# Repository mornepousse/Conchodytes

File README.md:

<h1 align="center">Conchodytes</h1>

<p align="center">
  <em>The shrimp that lives inside another's shell.</em><br>
  <em>La crevette qui vit dans la coquille d'un autre.</em>
</p>

---

## Firmware

The mouse runs the [KeSp firmware](https://github.com/mornepousse/KeSp_firmware)
(role `MOUSE`: PMW3389, three clicks, wheel, HID relayed to the dongle's slot 2).
Since 2026-09-21 **its board lives here**, not in the firmware repository:

- `boards/conchodytes/` — `board.h` (pinout, netlist-checked), `sdkconfig.defaults`,
  `test_pins.c` (the pinout contract);
- `firmware/` — the KeSp firmware as a git submodule, pinned on a release
  (`git submodule update --init`);
- `.github/workflows/firmware.yml` — calls the firmware's reusable workflow:
  every push builds `conchodytes_<version>.bin` (+ `_full.bin`), a `v*` tag
  publishes a release here.

```bash
scripts/test-pins.sh                                    # pinout contract, host, no toolchain
cd firmware && export IDF_COMPONENT_CHECK_NEW_VERSION=0 && \
idf.py -B build_conchodytes -DBOARD_DIR=../boards/conchodytes -DSDKCONFIG=build_conchodytes/sdkconfig build
esptool --chip esp32s3 -p /dev/ttyACM0 write_flash 0x20000 build_conchodytes/KeSp.bin
```

To take a newer firmware: `cd firmware && git fetch --tags && git checkout vX.Y.Z`,
then commit the submodule bump; read the firmware's release notes first (a
board macro may have been added — the pin contract will say).

## Firmware

The mouse runs the [KeSp firmware](https://github.com/mornepousse/KeSp_firmware)
(role `MOUSE`). Its board definition, pinout contract and firmware releases live
in **[Conchodytes-firmware](https://github.com/mornepousse/Conchodytes-firmware)**;
this repository is the hardware (PCB, notes, bring-up).

## English

A **sleeper mouse**: a replacement PCB for a Logitech M100 shell, keeping the
outer appearance of a cheap office mouse while carrying a **PMW3389** sensor and
a **wireless link to the [KeSp dongle](https://github.com/mornepousse/KeSp_dongle)** — the same receiver as the
[Niphargus](https://github.com/mornepousse/Niphargus) keyboard.

The shell is a fixed constraint: click switches, optical wheel encoder and sensor
positions are imposed by the M100 case and are locked in the layout.

Electronics reuse the reviewed and routed blocks of Niphargus — ESP32-S3 +
nRF24L01+, TP4056 charging with DW01A/FS8205 protection, HT7833 LDO, USB-C with
ESD protection.

## Français

Une **souris sleeper** : un PCB de remplacement pour coque Logitech M100, qui
garde l'apparence d'une souris de bureau bon marché tout en embarquant un capteur
**PMW3389** et une **liaison sans fil vers le [dongle KeSp](https://github.com/mornepousse/KeSp_dongle)** — le même récepteur
que le clavier [Niphargus](https://github.com/mornepousse/Niphargus).

La coque est une contrainte figée : les positions des clics, de l'encodeur
optique de molette et du capteur sont imposées par le boîtier M100, et
verrouillées dans le layout.

L'électronique reprend les blocs relus et routés du Niphargus — ESP32-S3 +
nRF24L01+, charge TP4056 avec protection DW01A/FS8205, LDO HT7833, USB-C protégé.

**État (2026-08-25)** — capteur **validé au banc** : identifié, SROM téléversé,
déplacement lu, sur trois reworks (voir `NOTES-V2.md`). Le firmware de banc est
dans `bringup/`.

**État (2026-08-07)** — schéma complet et vérifié par netlist, board **routé,
0 pad non connecté**. Le contour et les positions imposées par la coque viennent
du fork `USB-Mouse` ; l'alimentation, la charge, l'USB et la radio sont repris
du Niphargus. Reste à nettoyer le DRC (18 `copper_edge_clearance`) et à mesurer
la coque pour figer le contour définitif.

---

## Repository layout · Organisation

| Path | Contents |
|---|---|
| `hardware/pcb/` | KiCad project — `conchodytes.kicad_pro` |
| `scripts/` | Anti-regression checks (same pipeline as Niphargus) |
| `docs/` | Design notes |

### Fabrication

The two projects stay **independent**. They are only merged **at gerber export
time**, so the mouse board is panelised into the free space of the Niphargus
panel and costs almost nothing to make.

Les deux projets restent **indépendants**. Ils ne sont réunis qu'**au moment de
l'export gerber**, la carte souris venant se loger dans le vide du panneau
Niphargus — le PCB revient alors à presque rien.

### Anti-regression · Anti-régression

```sh
./scripts/check.sh --fast   # ERC vs committed baseline
./scripts/check.sh          # + full DRC
```

### Bloc capteur

| | |
|---|---|
| **PMW3389** | SPI partagé avec le nRF24 (`SCK_L`/`MOSI_L`/`MISO_L`), plus `SNS_NCS` et `SNS_MOTION`. Mode SPI **3**, `fSCLK` ≤ 2 MHz |
| **Alimentation** | ⚠️ VDD et VDDPIX **ne sont pas en 3,3 V** — rail dédié **2,0 V** par LDO (1,80-2,10 V, maximum **absolu** 2,10). VDDIO reste en 3,3 V |
| **Optique** | lentille **LM19-LSI**, commune au PMW3360 et au PMW3389 — celle d'origine de la M100 est faite pour le PAW3526 et ne convient pas |
| **Molette** | encodeur **optique** : LD1 éclaire une roue à 60 fentes, LQ1 la lit. ⚠️ `LQ1` (marquage `H6Y07`) est un capteur **VCC / GND / DATA**, PAS un double phototransistor — la v1 le câblait à l'envers, voir `NOTES-V2.md` §1bis |
| **Clics** | SPDT, COM à la masse, **NO et NC** tirés chacun au 3,3 V — lire les deux contacts en parallèle supprime le rebond |

Affectation des GPIO du S3, en évitant les broches de strapping :

| Signal | GPIO | Broche du module | | Signal | GPIO | Broche |
|---|---|---|---|---|---|---|
| `SNS_NCS` | 17 | 10 | | `SW_LEFT` | 10 | 18 |
| `SNS_MOTION` | 18 | 11 | | `SW_RIGHT` | 11 | 19 |
| `ENC_A` (DATA) | 7 | 7 | | `SW_MID` | 12 | 20 |
| `ENC_LED` ¹ | 9 | 17 | | `SW_LEFT_NC` | 5 | 5 |
| | | | | `SW_RIGHT_NC` | 4 | 4 |
| | | | | `SW_MID_NC` | 6 | 6 |

¹ `GPIO9` portait `ENC_B` en v1, sur un montage faux. En v2 il **commande la
cathode de LD1** — la LED de molette peut donc être éteinte par le firmware,
ce qui compte sur une souris à batterie. `ENC_A` (GPIO7) est le seul signal de
l'encodeur, et c'est `ADC1_CH6`.

⚠️ Ne pas confondre **GPIO** et **numéro de broche du module** : ce tableau
donnait auparavant les broches en les présentant comme des GPIO.

⚠️ **`SW_LEFT_NC` et `SW_RIGHT_NC` étaient inversés ici** jusqu'au 2026-08-25.
Le tableau annonçait GPIO4 à gauche et GPIO5 à droite ; la netlist dit l'inverse
— GPIO4 va à `SW2.3` (clic droit, R109) et GPIO5 à `SW1.3` (clic gauche, R108).
Comme l'anti-rebond apparie NO et NC du **même** bouton, écrire le firmware sur
l'ancien tableau croisait les deux clics.

Le reste du brochage, relevé à la netlist au `kicad-cli` le 2026-08-25 :

| Signal | Broche | GPIO | | Signal | Broche | GPIO |
|---|---|---|---|---|---|---|
| `SCK_L` | 31 | 38 | | `CSN_1` (nRF) | 38 | 2 |
| `MISO_L` | 32 | 39 | | `CE_1` (nRF) | 39 | 1 |
| `MOSI_L` | 33 | 40 | | `IRQ_1` (nRF) | 34 | 41 |
| `VBAT_SENSE` ² | 21 | 13 (ADC2_CH2) | | `D-` / `D+` | 13 / 14 | 19 / 20 |
| J1 `TX` / `RX` | 37 / 36 | 43 / 44 | | J1 `IO0` | 27 | 0 |

² En **v2**, `VBAT_SENSE` passe sur la broche 12 = **GPIO8 = ADC1_CH7**. L'ADC2
de l'ESP32-S3 est partagé avec le driver Wi-Fi ; tant que la mesure y reste, le
Wi-Fi est interdit sur cette carte. Voir `NOTES-V2.md` point 7.

Les lignes SPI et de contrôle portent chacune 100 Ω en série (R16/R18/R30,
R36/R39/R41) — sans effet à 2 MHz.

Les contacts NC des trois clics sont câblés sur GPIO4/5/6, chacun avec son
pull-up 10 k (R108-R110). Au repos NC est fermé sur COM donc bas, NO ouvert donc
haut ; au clic ils s'inversent. **Pendant le rebond les deux sont hauts** — le
firmware garde alors l'état précédent, ce qui élimine le double-clic sans aucun
filtrage temporel.

Les six empreintes imposées par la coque — SW1/SW2/SW3, LD1, LQ1, U2 — sont
**verrouillées** dans le layout et liées à leurs symboles. Ne pas les renommer :
le F8 les dissocierait et leurs positions seraient perdues.

## Historique · History

| Étape | Ce qui s'est passé |
|---|---|
| **REV1** | Premier tirage. Trois défauts de conception trouvés au banc, tous documentés dans `NOTES-V2.md` : `LQ1` câblé à l'envers (§1bis), `U100` — le LDO du capteur — pattes 2 et 3 croisées, et `U2` monté à 180°. |
| **2026-08-25** | Bring-up du capteur. La puce n'est **pas** un PMW3360 mais un **PMW3389** (`Product_ID = 0x47`) : identité lue, SROM téléversé, déplacement mesuré. Rail capteur corrigé au fer, **2,01 V mesuré**. Rotation de 180° confirmée par la mesure — les deux axes inversés, biais 100 % sur 76 échantillons. |
| **REV2.0.0** | Schéma corrigé et gerbers partis en fabrication : `LQ1` recâblé sur `+3V3`, `D100` supprimée, `VBAT_SENSE` déplacé sur ADC1, `U100` corrigé, `LD1` passée en cathode pilotée. |
| **2026-08-26** | Firmware complet et lien radio. La souris parle au dongle KaSe sur le slot RF 2 — le code vit comme septième variante de carte dans `KeSp_firmware`, pas dans un dépôt séparé. |

### Ce que la mise au point du 26 août a trouvé

Quatre défauts, chacun établi par une mesure prise **aux deux extrémités du
lien** — compteurs de la souris d'un côté, `RF_STATUS` du dongle de l'autre.

| Défaut | Avant | Après |
|---|---|---|
| Bascule de mode SPI sous un CS déjà abaissé — bus partagé entre le capteur (mode 3) et la radio (mode 0) | 1 trame acquittée sur 738 | 693 sur 693 |
| Scrutation du dongle à 10 ms, pour une FIFO nRF24 de 3 paquets | 3135 acceptées sur 8356 (37,5 %) | 99-100 % |
| Déplacement des trames non acquittées **jeté** au lieu d'être réaccumulé | la moitié du geste disparaissait | distance conservée |
| Résolution jamais écrite : la puce restait à son défaut | 5000 cpi | 1000 cpi, comme la M100 |

### Ce qui reste ouvert

Un tremblement d'**origine optique** que le firmware ne peut pas corriger :
`SQUAL` mesuré entre 30 et 55 là où ~80 est attendu, et le capteur produit sur
certaines surfaces des dérives cohérentes de ~1000 comptes en trois secondes,
souris immobile — indiscernables d'un geste lent volontaire.

Deux pistes, par ordre de coût croissant, détaillées au **§8 de `NOTES-V2.md`** :

1. **`R102`** vaut 330 Ω sous 3,3 V, soit ~6,8 mA dans `LD1`, quand la M100
   d'origine en fait passer 2,6 mA. La LED de molette tourne à près du triple de
   son intensité prévue, en permanence, contre le capteur. **820 Ω** reproduit
   le point de fonctionnement d'origine. Un composant.
2. **Le montage à 180° de `U2`** échange peut-être les chemins d'illumination et
   d'imagerie de la lentille, ce qui expliquerait l'image à la fois sombre en
   moyenne et saturée par endroits. Si c'est le cas, la rotation d'empreinte
   prévue en REV2 corrige le tremblement **et** le sens des axes d'un coup.

## Credits

Outline and mechanical positions derive from
[RandomDelta6/USB-Mouse](https://github.com/RandomDelta6/USB-Mouse), a working
USB mouse PCB reusing the original optical assembly.

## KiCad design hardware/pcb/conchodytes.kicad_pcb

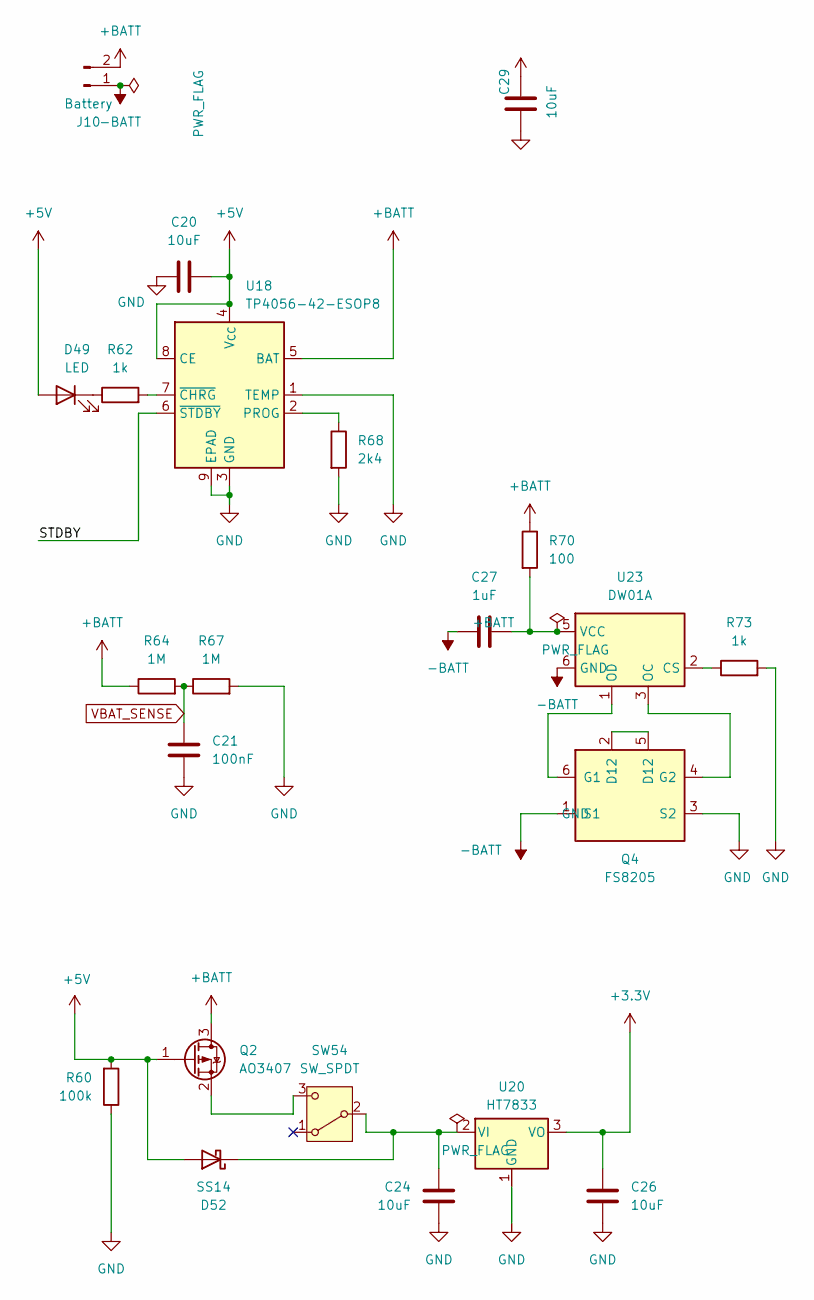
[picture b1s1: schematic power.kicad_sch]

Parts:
C20, C24, C26, C29: 10uF; C_1206_3216Metric_Pad1.33x1.80mm_HandSolder
C21: 100nF; C_0603_1608Metric_Pad1.08x0.95mm_HandSolder
C27: 1uF; C_0805_2012Metric_Pad1.18x1.45mm_HandSolder
D49: LED; LED_0805_2012Metric_Pad1.15x1.40mm_HandSolder
D52: SS14; D_SMA; LCSC C2480
J10: Battery; PinHeader_1x02_P2.54mm_Vertical
Q2: AO3407; SOT-23; LCSC C351408
Q4: FS8205; SOT-23-6; LCSC C32254
R60: 100k; R_0603_1608Metric_Pad0.98x0.95mm_HandSolder
R62, R73: 1k; R_0805_2012Metric_Pad1.20x1.40mm_HandSolder
R64, R67: 1M; R_0805_2012Metric_Pad1.20x1.40mm_HandSolder
R68: 2k4; R_0805_2012Metric_Pad1.20x1.40mm_HandSolder
R70: 100; R_0603_1608Metric_Pad0.98x0.95mm_HandSolder
SW54: SW_SPDT; SW_SPDT_PCM12; LCSC C431540
U18: TP4056-42-ESOP8; SOIC-8-1EP_3.9x4.9mm_P1.27mm_EP2.41x3.3mm_ThermalVias; LCSC C16581
U20: HT7833; SOT-89-3; LCSC C50936
U23: DW01A; SOT-23-6; LCSC C351410

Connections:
+3.3V: C26.2, U20.3 (VO); also elsewhere on the board
+5V: C20.2, D49.2 (A), D52.2 (A), Q2.1 (G), R60.2, U18.4 (V_{CC}), U18.8 (CE); also elsewhere on the board
+BATT: C29.1, J10.2, Q2.3 (D), R64.1, R70.1, U18.5 (BAT)
-BATT: C27.2, J10.1, Q4.1 (S1), U23.6 (GND)
/power/STDBY: U18.6 (~STDBY)
GND: C20.1, C21.1, C24.1, C26.1, C29.2, Q4.3 (S2), R60.1, R67.2, R68.2, R73.2, U18.1 (TEMP), U18.3 (GND), U18.9 (EPAD), U20.1 (GND); also elsewhere on the board
unnamed: D49.1 (K), R62.1
unnamed: C24.2, D52.1 (K), SW54.2 (B), U20.2 (VI)
unnamed: Q2.2 (S), SW54.3 (C)
unnamed: Q4.2 (D12), Q4.5 (D12)
unnamed: Q4.6 (G1), U23.1 (OD)
unnamed: Q4.4 (G2), U23.3 (OC)
unnamed: R68.1, U18.2 (PROG)
unnamed: R62.2, U18.7 (~CHRG)
unnamed: R73.1, U23.2 (CS)
unnamed: C27.1, R70.2, U23.5 (VCC)
VBAT_SENSE: C21.2, R64.2, R67.1; also elsewhere on the board

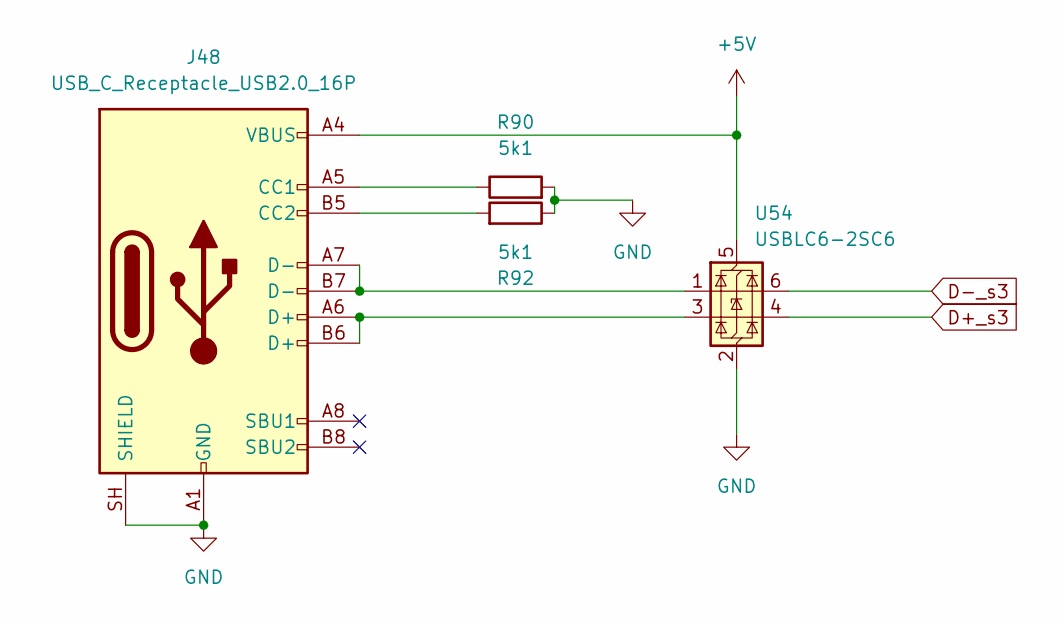
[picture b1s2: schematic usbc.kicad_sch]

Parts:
J48: USB_C_Receptacle_USB2.0_16P; USB_C_Receptacle_HRO_TYPE-C-31-M-12; LCSC C165948
R90, R92: 5k1; R_0603_1608Metric_Pad0.98x0.95mm_HandSolder
U54: USBLC6-2SC6; SOT-23-6; LCSC C7519

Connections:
+5V: J48.A4 (VBUS), J48.A9 (VBUS), J48.B4 (VBUS), J48.B9 (VBUS), U54.5 (VBUS); also elsewhere on the board
D+_s3: U54.4 (I/O2); also elsewhere on the board
D-_s3: U54.6 (I/O1); also elsewhere on the board
GND: J48.A1 (GND), J48.A12 (GND), J48.B1 (GND), J48.B12 (GND), J48.SH (SHIELD), R90.2, R92.1, U54.2 (GND); also elsewhere on the board
unnamed: J48.A5 (CC1), R90.1
unnamed: J48.B5 (CC2), R92.2
unnamed: J48.A6 (D+), J48.B6 (D+), U54.3 (I/O2)
unnamed: J48.A7 (D-), J48.B7 (D-), U54.1 (I/O1)

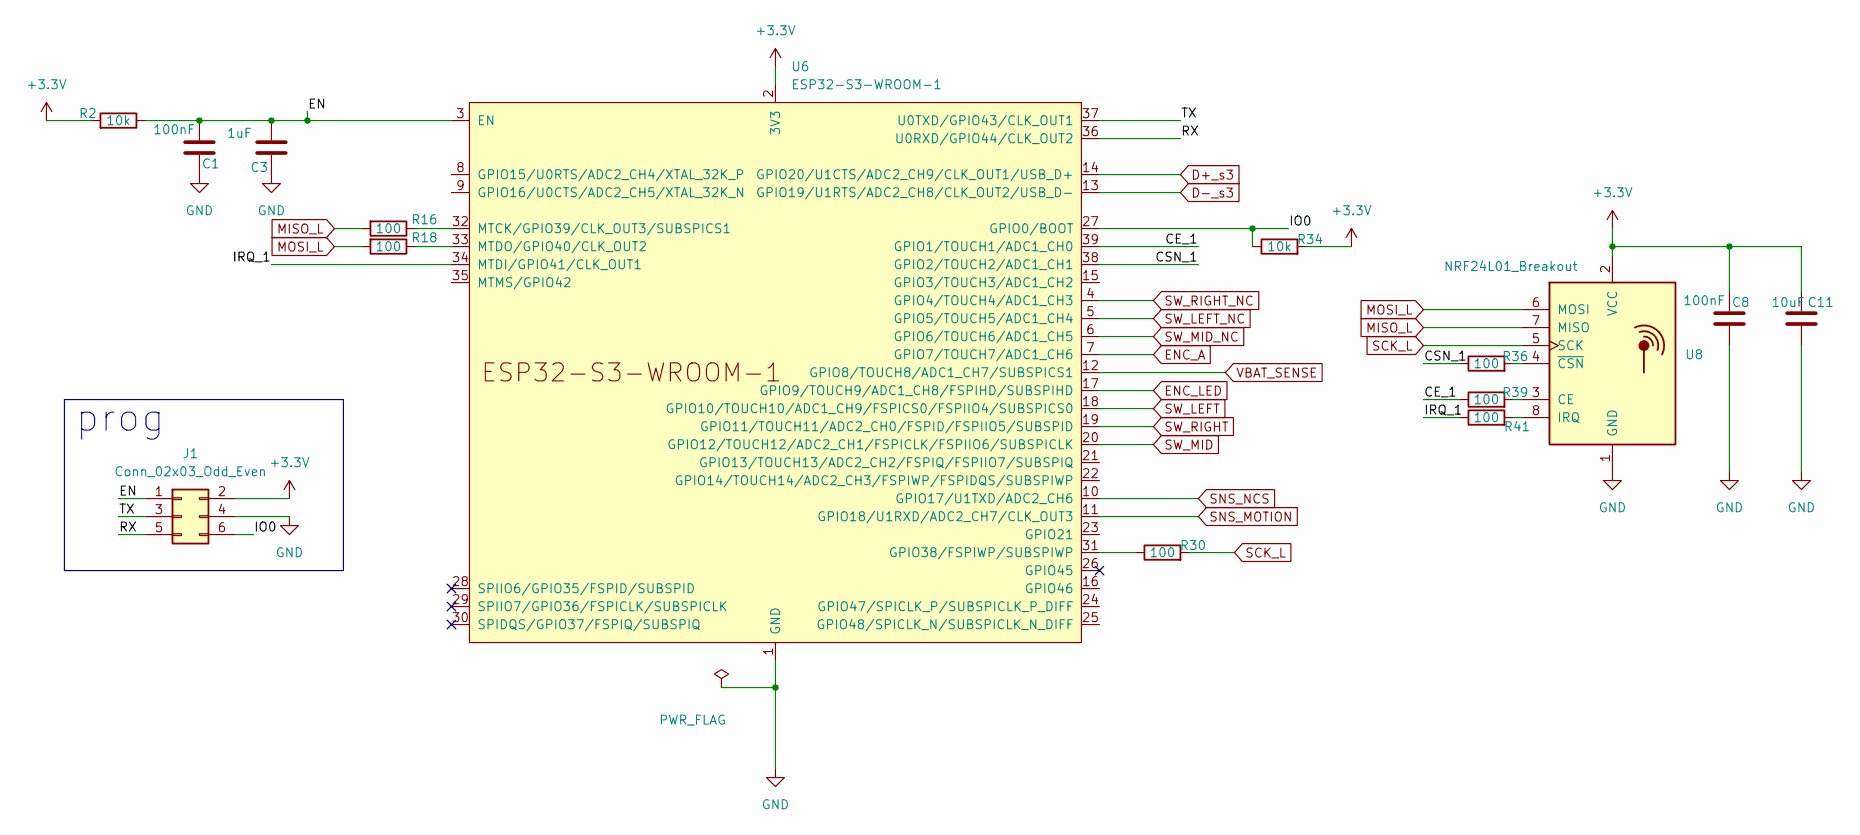
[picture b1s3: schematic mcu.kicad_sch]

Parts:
C1, C8: 100nF; C_0603_1608Metric_Pad1.08x0.95mm_HandSolder
C3: 1uF; C_0805_2012Metric_Pad1.18x1.45mm_HandSolder
C11: 10uF; C_1206_3216Metric_Pad1.33x1.80mm_HandSolder
J1: Conn_02x03_Odd_Even; PinHeader_2x03_P1.27mm_Vertical
R2, R34: 10k; R_0603_1608Metric_Pad0.98x0.95mm_HandSolder
R16, R18, R30, R36, R39, R41: 100; R_0603_1608Metric_Pad0.98x0.95mm_HandSolder
U6: ESP32-S3-WROOM-1; ESP32-S3-WROOM-1U; LCSC C2913204
U8: NRF24L01_Breakout; NRF24L01

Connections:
+3.3V: C8.2, C11.2, J1.2, R2.2, R34.2, U6.2 (3V3), U8.2 (VCC); also elsewhere on the board
/mcu/CE_1: R39.1, U6.39 (GPIO1/TOUCH1/ADC1_CH0)
/mcu/CSN_1: R36.1, U6.38 (GPIO2/TOUCH2/ADC1_CH1)
/mcu/EN: C1.2, C3.2, J1.1, R2.1, U6.3 (EN)
/mcu/IO0: J1.6, R34.1, U6.27 (GPIO0/BOOT)
/mcu/IRQ_1: R41.1, U6.34 (MTDI/GPIO41/CLK_OUT1)
/mcu/RX: J1.5, U6.36 (U0RXD/GPIO44/CLK_OUT2)
/mcu/TX: J1.3, U6.37 (U0TXD/GPIO43/CLK_OUT1)
D+_s3: U6.14 (GPIO20/U1CTS/ADC2_CH9/CLK_OUT1/USB_D+); also elsewhere on the board
D-_s3: U6.13 (GPIO19/U1RTS/ADC2_CH8/CLK_OUT2/USB_D-); also elsewhere on the board
ENC_A: U6.7 (GPIO7/TOUCH7/ADC1_CH6); also elsewhere on the board
ENC_LED: U6.17 (GPIO9/TOUCH9/ADC1_CH8/FSPIHD/SUBSPIHD); also elsewhere on the board
GND: C1.1, C3.1, C8.1, C11.1, J1.4, U6.1 (GND), U6.40 (GND), U6.41 (GND), U8.1 (GND); also elsewhere on the board
MISO_L: R16.2, U8.7 (MISO); also elsewhere on the board
MOSI_L: R18.2, U8.6 (MOSI); also elsewhere on the board
unnamed: R30.1, U6.31 (GPIO38/FSPIWP/SUBSPIWP)
unnamed: R16.1, U6.32 (MTCK/GPIO39/CLK_OUT3/SUBSPICS1)
unnamed: R18.1, U6.33 (MTDO/GPIO40/CLK_OUT2)
unnamed: R39.2, U8.3 (CE)
unnamed: R41.2, U8.8 (IRQ)
unnamed: R36.2, U8.4 (~CSN)
SCK_L: R30.2, U8.5 (SCK); also elsewhere on the board
SNS_MOTION: U6.11 (GPIO18/U1RXD/ADC2_CH7/CLK_OUT3); also elsewhere on the board
SNS_NCS: U6.10 (GPIO17/U1TXD/ADC2_CH6); also elsewhere on the board
SW_LEFT: U6.18 (GPIO10/TOUCH10/ADC1_CH9/FSPICS0/FSPIIO4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); also elsewhere on the board
SW_LEFT_NC: U6.5 (GPIO5/TOUCH5/ADC1_CH4); also elsewhere on the board
SW_MID: U6.20 (GPIO12/TOUCH12/ADC2_CH1/FSPICLK/FSPIIO6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); also elsewhere on the board
SW_MID_NC: U6.6 (GPIO6/TOUCH6/ADC1_CH5); also elsewhere on the board
SW_RIGHT: U6.19 (GPIO11/TOUCH11/ADC2_CH0/FSPID/FSPIIO5/S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); also elsewhere on the board
SW_RIGHT_NC: U6.4 (GPIO4/TOUCH4/ADC1_CH3); also elsewhere on the board
VBAT_SENSE: U6.12 (GPIO8/TOUCH8/ADC1_CH7/SUBSPICS1); also elsewhere on the board

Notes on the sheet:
prog

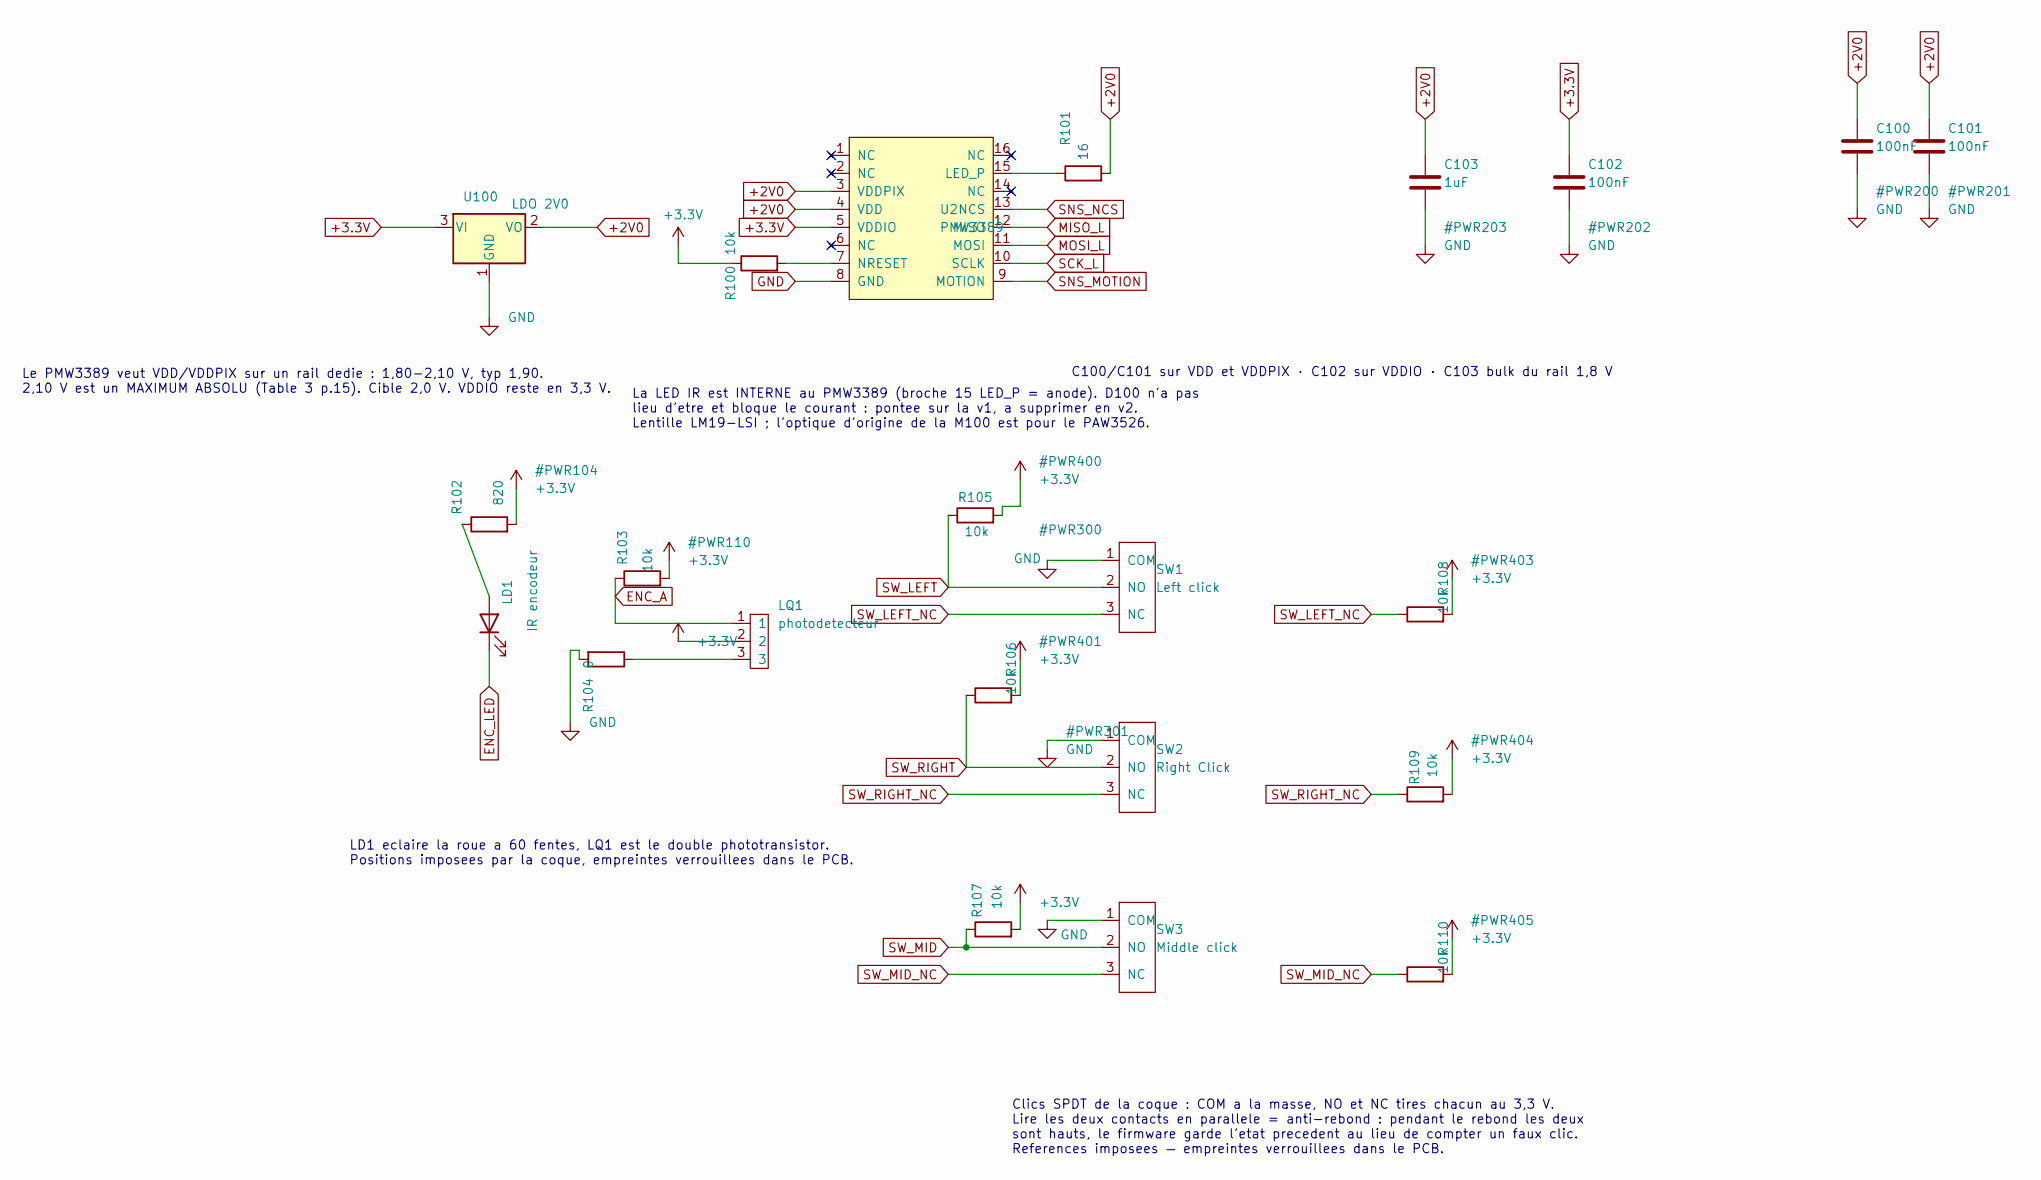
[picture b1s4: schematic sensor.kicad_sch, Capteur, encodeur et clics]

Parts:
C100, C101, C102: 100nF; C_0603_1608Metric
C103: 1uF; C_0603_1608Metric
LD1: IR encodeur; Rot_LED
LQ1: photodetecteur; LQ1
R100, R103, R105, R106, R107, R108, R109, R110: 10k; R_0603_1608Metric
R101: 16; R_0603_1608Metric
R102: 820; R_0603_1608Metric
R104: 0; R_0603_1608Metric
SW1: Left click; SPDT_Switch
SW2: Right Click; SPDT_Switch
SW3: Middle click; SPDT_Switch
U2: PMW3389; PMW3360
U100: LDO 2V0; SOT-23

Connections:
+2V0: C100.1, C101.1, C103.1, R101.2, U2.3 (VDDPIX), U2.4 (VDD), U100.2 (VO)
+3.3V: C102.1, LQ1.2, R100.1, R102.2, R103.2, R105.2, R106.2, R107.2, R108.2, R109.2, R110.2, U2.5 (VDDIO), U100.3 (VI); also elsewhere on the board
ENC_A: LQ1.1, R103.1; also elsewhere on the board
ENC_LED: LD1.1 (K); also elsewhere on the board
GND: C100.2, C101.2, C102.2, C103.2, R104.2, SW1.1 (COM), SW2.1 (COM), SW3.1 (COM), U2.8 (GND), U100.1 (GND); also elsewhere on the board
MISO_L: U2.12 (MISO); also elsewhere on the board
MOSI_L: U2.11 (MOSI); also elsewhere on the board
unnamed: LD1.2 (A), R102.1
unnamed: LQ1.3, R104.1
unnamed: R101.1, U2.15 (LED_P)
unnamed: R100.2, U2.7 (NRESET)
SCK_L: U2.10 (SCLK); also elsewhere on the board
SNS_MOTION: U2.9 (MOTION); also elsewhere on the board
SNS_NCS: U2.13 (NCS); also elsewhere on the board
SW_LEFT: R105.1, SW1.2 (NO); also elsewhere on the board
SW_LEFT_NC: R108.1, SW1.3 (NC); also elsewhere on the board
SW_MID: R107.1, SW3.2 (NO); also elsewhere on the board
SW_MID_NC: R110.1, SW3.3 (NC); also elsewhere on the board
SW_RIGHT: R106.1, SW2.2 (NO); also elsewhere on the board
SW_RIGHT_NC: R109.1, SW2.3 (NC); also elsewhere on the board

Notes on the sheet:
C100/C101 sur VDD et VDDPIX · C102 sur VDDIO · C103 bulk du rail 1,8 V
Clics SPDT de la coque : COM a la masse, NO et NC tires chacun au 3,3 V. Lire les deux contacts en parallele = anti-rebond : pendant le rebond les deux sont hauts, le firmware garde l'etat precedent au lieu de compter un faux clic. References imposees — empreintes verrouillees dans le PCB.
La LED IR est INTERNE au PMW3389 (broche 15 LED_P = anode). D100 n'a pas lieu d'etre et bloque le courant : pontee sur la v1, a supprimer en v2. Lentille LM19-LSI ; l'optique d'origine de la M100 est pour le PAW3526.
Le PMW3389 veut VDD/VDDPIX sur un rail dedie : 1,80-2,10 V, typ 1,90. 2,10 V est un MAXIMUM ABSOLU (Table 3 p.15). Cible 2,0 V. VDDIO reste en 3,3 V.
LD1 eclaire la roue a 60 fentes, LQ1 est le double phototransistor. Positions imposees par la coque, empreintes verrouillees dans le PCB.

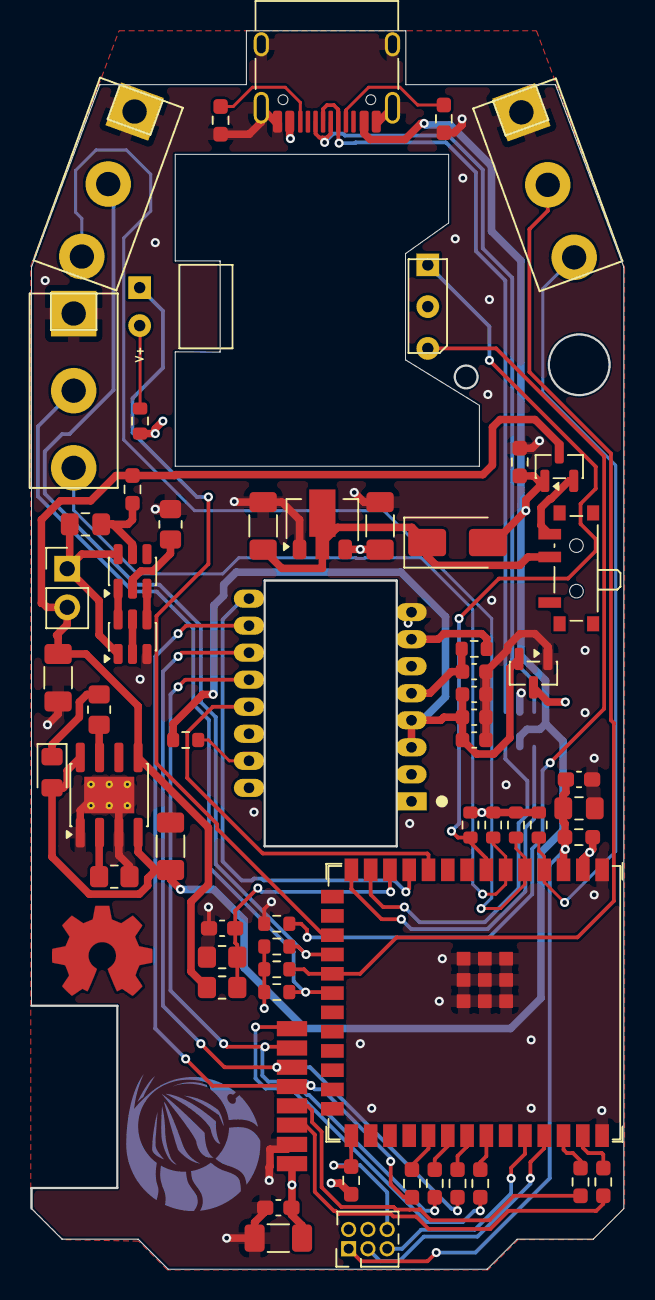
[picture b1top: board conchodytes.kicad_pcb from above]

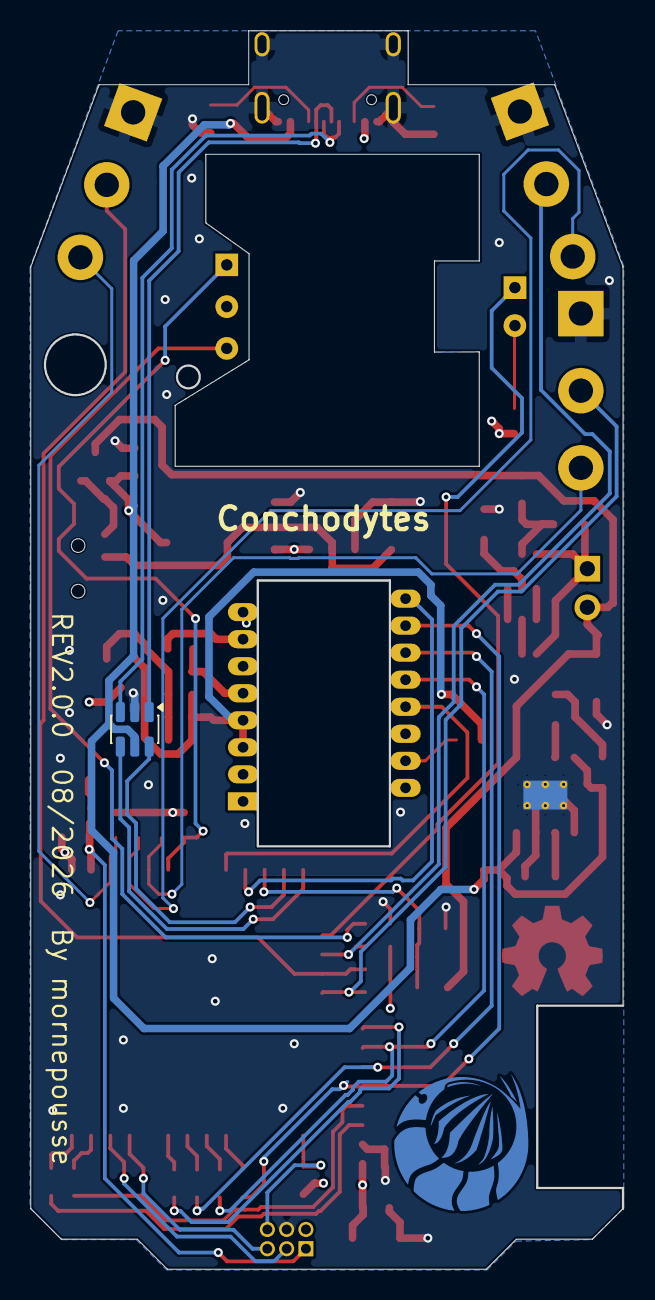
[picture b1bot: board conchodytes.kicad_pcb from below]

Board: 4 copper layers, 39.0 x 81.5 mm, 65 parts (2 on the bottom side), 53 nets.

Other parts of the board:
HS1: nephargus_10mm_Cu; Niphargus_10mm_Cu
HS2: OSHW-Symbol_6.7x6mm_Copper

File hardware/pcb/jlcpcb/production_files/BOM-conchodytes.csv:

Comment,Designator,Footprint,LCSC,Quantity
AO3407,Q2,SOT-23,C351408,1
DW01A,U23,SOT-23-6,C351410,1
ESP32-S3-WROOM-1,U6,ESP32-S3-WROOM-1U,C2913204,1
FS8205,Q4,SOT-23-6,C32254,1
HT7833,U20,SOT-89-3,C50936,1
SS14,D52,D_SMA,C2480,1
SW_SPDT,SW54,SW_SPDT_PCM12,C431540,1
TP4056-42-ESOP8,U18,SOIC-8-1EP_3.9x4.9mm_P1.27mm_EP2.41x3.3mm_ThermalVias,C16581,1
USBLC6-2SC6,U54,SOT-23-6,C7519,1
USB_C_Receptacle_USB2.0_16P,J48,USB_C_Receptacle_HRO_TYPE-C-31-M-12,C165948,1
IR encodeur,LD1,Rot_LED,,1
Left click,SW1,SPDT_Switch,,1
Middle click,SW3,SPDT_Switch,,1
Right Click,SW2,SPDT_Switch,,1
photodetecteur,LQ1,LQ1,,1
5k1,R92,R_0603_1608Metric_Pad0.98x0.95mm_HandSolder,,1
1M,R67,R_0805_2012Metric_Pad1.20x1.40mm_HandSolder,,1
820,R102,R_0603_1608Metric,,1
10k,R107,R_0603_1608Metric,,1
10k,R110,R_0603_1608Metric,,1
100,R39,R_0603_1608Metric_Pad0.98x0.95mm_HandSolder,,1
PMW3389,U2,PMW3360,,1
100nF,C8,C_0603_1608Metric_Pad1.08x0.95mm_HandSolder,,1
1M,R64,R_0805_2012Metric_Pad1.20x1.40mm_HandSolder,,1
10k,R109,R_0603_1608Metric,,1
100nF,C21,C_0603_1608Metric_Pad1.08x0.95mm_HandSolder,,1
1uF,C103,C_0603_1608Metric,,1
1k,R62,R_0805_2012Metric_Pad1.20x1.40mm_HandSolder,,1
100nF,C1,C_0603_1608Metric_Pad1.08x0.95mm_HandSolder,,1
NRF24L01_Breakout,U8,NRF24L01,,1
100nF,C100,C_0603_1608Metric,,1
Battery,J10,PinHeader_1x02_P2.54mm_Vertical,,1
10uF,C11,C_1206_3216Metric_Pad1.33x1.80mm_HandSolder,,1
10uF,C29,C_1206_3216Metric_Pad1.33x1.80mm_HandSolder,,1
100,R70,R_0603_1608Metric_Pad0.98x0.95mm_HandSolder,,1
1k,R73,R_0805_2012Metric_Pad1.20x1.40mm_HandSolder,,1
100nF,C101,C_0603_1608Metric,,1
Conn_02x03_Odd_Even,J1,PinHeader_2x03_P1.27mm_Vertical,,1
100nF,C102,C_0603_1608Metric,,1
100k,R60,R_0603_1608Metric_Pad0.98x0.95mm_HandSolder,,1
100,R16,R_0603_1608Metric_Pad0.98x0.95mm_HandSolder,,1
10k,R105,R_0603_1608Metric,,1
1uF,C27,C_0805_2012Metric_Pad1.18x1.45mm_HandSolder,,1
100,R18,R_0603_1608Metric_Pad0.98x0.95mm_HandSolder,,1
16,R101,R_0603_1608Metric,,1
LDO 2V0,U100,SOT-23,,1
10uF,C20,C_1206_3216Metric_Pad1.33x1.80mm_HandSolder,,1
1uF,C3,C_0805_2012Metric_Pad1.18x1.45mm_HandSolder,,1
10k,R34,R_0603_1608Metric_Pad0.98x0.95mm_HandSolder,,1
5k1,R90,R_0603_1608Metric_Pad0.98x0.95mm_HandSolder,,1
10k,R108,R_0603_1608Metric,,1
0,R104,R_0603_1608Metric,,1
100,R30,R_0603_1608Metric_Pad0.98x0.95mm_HandSolder,,1
100,R41,R_0603_1608Metric_Pad0.98x0.95mm_HandSolder,,1
10k,R2,R_0603_1608Metric_Pad0.98x0.95mm_HandSolder,,1
10k,R100,R_0603_1608Metric,,1
LED,D49,LED_0805_2012Metric_Pad1.15x1.40mm_HandSolder,,1
10uF,C26,C_1206_3216Metric_Pad1.33x1.80mm_HandSolder,,1
100,R36,R_0603_1608Metric_Pad0.98x0.95mm_HandSolder,,1
2k4,R68,R_0805_2012Metric_Pad1.20x1.40mm_HandSolder,,1
10uF,C24,C_1206_3216Metric_Pad1.33x1.80mm_HandSolder,,1
10k,R106,R_0603_1608Metric,,1
10k,R103,R_0603_1608Metric,,1
nephargus_10mm_Cu,HS1,Niphargus_10mm_Cu,,1

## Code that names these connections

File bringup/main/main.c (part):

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 * Pas de radio, pas de HID, pas de keymap. Sortie sur UART0 (J1).
 *
 * Brochage releve a la netlist de hardware/pcb/ au kicad-cli :
 *   SCK_L  = GPIO38   MISO_L = GPIO39   MOSI_L = GPIO40   (100 R en serie)
 *   SNS_NCS = GPIO17  SNS_MOTION = GPIO18
 *   nRF24 : CSN = GPIO2, CE = GPIO1  -> maintenus inactifs, bus partage.
 *
 * Datasheet PMW3389DM-T3QU, PixArt, Version 1.0 | 07 sep 2017 :
 *   Product_ID (0x00)         = 0x47   p. 20
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#define PIN_SCK        GPIO_NUM_38
#define PIN_MISO       GPIO_NUM_39
#define PIN_MOSI       GPIO_NUM_40
#define PIN_SNS_NCS    GPIO_NUM_17
#define PIN_SNS_MOTION GPIO_NUM_18
#define PIN_NRF_CSN    GPIO_NUM_2
#define PIN_NRF_CE     GPIO_NUM_1
#define PIN_NRF_IRQ    GPIO_NUM_41

/* Clics : trois SPDT, COM a la masse, NO et NC tires chacun au 3,3 V par 10 k
 * (R105-R107 et R108-R110). ATTENTION : le README annoncait LEFT_NC sur GPIO4
 * et RIGHT_NC sur GPIO5 — c'est l'inverse. Valeurs ci-dessous relevees a la
 * netlist : GPIO4 va a SW2.3 (clic DROIT), GPIO5 a SW1.3 (clic GAUCHE). */
#define PIN_SW_LEFT       GPIO_NUM_10
#define PIN_SW_LEFT_NC    GPIO_NUM_5
#define PIN_SW_RIGHT      GPIO_NUM_11
#define PIN_SW_RIGHT_NC   GPIO_NUM_4
#define PIN_SW_MID        GPIO_NUM_12
#define PIN_SW_MID_NC     GPIO_NUM_6

/* Molette : encodeur optique, LD1 eclaire une roue a 60 fentes, LQ1 double
 * phototransistor -> deux voies en quadrature. */
#define PIN_ENC_A      GPIO_NUM_7
#define PIN_ENC_B      GPIO_NUM_9

#define SNS_SPI_HOST   SPI2_HOST
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 * donnee, or tSRAD tombe justement dans cet intervalle. D'ou spics_io_num = -1
 * et ces deux fonctions. Meme geste que main/comm/rf/rf_driver.c cote KeSp. */

static inline void cs_low(void)  { gpio_set_level(PIN_SNS_NCS, 0); esp_rom_delay_us(1); }
static inline void cs_high(void) { esp_rom_delay_us(1); gpio_set_level(PIN_SNS_NCS, 1); }

static void spi_tx(const uint8_t *tx, uint8_t *rx, size_t len)
{
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} clic_t;

static clic_t s_clics[3] = {
    { PIN_SW_LEFT,  PIN_SW_LEFT_NC,  false, "G", 0, 0, 0, 0 },
    { PIN_SW_RIGHT, PIN_SW_RIGHT_NC, false, "D", 0, 0, 0, 0 },
    { PIN_SW_MID,   PIN_SW_MID_NC,   false, "M", 0, 0, 0, 0 },
};

/* Rend true si l'etat a change. Appelee a 1 kHz : sans ca la fenetre de rebond,
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static void wheel_task(void *arg)
{
    (void)arg;
    uint8_t prev = (uint8_t)((gpio_get_level(PIN_ENC_A) << 1) | gpio_get_level(PIN_ENC_B));
    while (1) {
        uint8_t cur = (uint8_t)((gpio_get_level(PIN_ENC_A) << 1) | gpio_get_level(PIN_ENC_B));
        if (cur != prev) {
            int8_t pas = QUAD[(prev << 2) | cur];
            if (pas) s_wheel += pas;
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 */
static void enc_drive_test(void)
{
    /* GPIO8 (broche 12 du module) est NON CONNECTE sur cette carte d'apres la
     * netlist : il sert de temoin. S'il ne se pilote pas non plus, c'est la
     * methode de mesure qui est fausse et pas le cablage. */
    const struct { gpio_num_t p; const char *n; } lignes[] = {
        { PIN_ENC_A,   "ENC_A  (GPIO7) " },
        { PIN_ENC_B,   "ENC_B  (GPIO9) " },
        /* Deux temoins, et le second vaut mieux que le premier :
         *   GPIO8 est NON CONNECTE — il ne prouve que le cas facile ;
         *   SW_LEFT porte un vrai tirage 10 k et un interrupteur vers la masse,
         *   soit exactement la topologie de ENC_A/ENC_B. S'il se pilote et pas
         *   eux, la difference n'est pas dans la methode. */
        { GPIO_NUM_8,  "TEMOIN libre   " },
        { PIN_SW_LEFT, "TEMOIN charge  " },
    };
    const gpio_drive_cap_t caps[] = {
        GPIO_DRIVE_CAP_0, GPIO_DRIVE_CAP_1, GPIO_DRIVE_CAP_2, GPIO_DRIVE_CAP_3,
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     * voies de l'encodeur — on n'arme pas ceux du S3, qui les mettraient en
     * parallele et fausseraient les seuils. */
    gpio_config_t in = {
        .pin_bit_mask = (1ULL << PIN_SW_LEFT)  | (1ULL << PIN_SW_LEFT_NC)  |
                        (1ULL << PIN_SW_RIGHT) | (1ULL << PIN_SW_RIGHT_NC) |
                        (1ULL << PIN_SW_MID)   | (1ULL << PIN_SW_MID_NC)   |
                        (1ULL << PIN_ENC_A)    | (1ULL << PIN_ENC_B),
        .mode         = GPIO_MODE_INPUT,
        .pull_up_en   = GPIO_PULLUP_DISABLE,
        .pull_down_en = GPIO_PULLDOWN_DISABLE,
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 *
 * IRQ est la plus parlante et elle est gratuite : c'est une SORTIE du nRF24,
 * active basse, donc HAUTE au repos. Si le module est alimente et vivant,
 * GPIO41 lit 1. S'il lit 0 ou flotte, l'alimentation ou le module sont en
 * cause, et CSN n'y est pour rien.
 *
 * CSN est teste dans les DEUX sens : une ligne qui ne peut pas descendre
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                      "module est bien la, mais dans un etat anormal.");

    const struct { gpio_num_t p; const char *n; } l[] = {
        { PIN_NRF_CSN, "CSN (GPIO2)" }, { PIN_NRF_CE, "CE  (GPIO1)" },
    };
    for (unsigned i = 0; i < 2; i++) {
        ESP_ERROR_CHECK(gpio_set_direction(l[i].p, GPIO_MODE_INPUT_OUTPUT));
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     * capteur repond, c'est deux esclaves qui tirent MISO. */
    gpio_config_t idle = {
        .pin_bit_mask = (1ULL << PIN_NRF_CSN) | (1ULL << PIN_NRF_CE) |
                        (1ULL << PIN_SNS_NCS),
        .mode         = GPIO_MODE_OUTPUT,
    };
    ESP_ERROR_CHECK(gpio_config(&idle));
    gpio_set_level(PIN_NRF_CSN, 1);      /* CSN inactif = haut */
    gpio_set_level(PIN_NRF_CE,  0);      /* radio au repos */
    gpio_set_level(PIN_SNS_NCS, 1);

    gpio_config_t motion = {
        .pin_bit_mask = 1ULL << PIN_SNS_MOTION,
        .mode         = GPIO_MODE_INPUT,
        .pull_up_en   = GPIO_PULLUP_ENABLE,
    };
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{
    ESP_LOGI(TAG, "Conchodytes bring-up capteur — PMW3389");
    ESP_LOGI(TAG, "SCK=%d MISO=%d MOSI=%d NCS=%d MOTION=%d @ %d Hz mode 3",
             PIN_SCK, PIN_MISO, PIN_MOSI, PIN_SNS_NCS, PIN_SNS_MOTION, SNS_CLOCK_HZ);

    bus_init();
    vTaskDelay(pdMS_TO_TICKS(50));
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
    input_init();
    ESP_LOGI(TAG, "clics G=%d/%d D=%d/%d M=%d/%d (NO/NC), molette A=%d B=%d",
             PIN_SW_LEFT, PIN_SW_LEFT_NC, PIN_SW_RIGHT, PIN_SW_RIGHT_NC,
             PIN_SW_MID, PIN_SW_MID_NC, PIN_ENC_A, PIN_ENC_B);

    int32_t wheel_prev = 0;
    unsigned tour = 0;
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        ESP_LOGI(TAG, "dx=%6d dy=%6d SQ=%3u Sh=%4u MOT=%d | G%d D%d M%d | "
                      "brut G%d%d D%d%d M%d%d | AB=%d%d molette %+4ld (tot %6ld, rat %lu)",
                 dx, dy, squal, ((unsigned)sh << 8) | sl,
                 gpio_get_level(PIN_SNS_MOTION),
                 s_clics[0].pressed, s_clics[1].pressed, s_clics[2].pressed,
                 gpio_get_level(PIN_SW_LEFT),  gpio_get_level(PIN_SW_LEFT_NC),
                 gpio_get_level(PIN_SW_RIGHT), gpio_get_level(PIN_SW_RIGHT_NC),
                 gpio_get_level(PIN_SW_MID),   gpio_get_level(PIN_SW_MID_NC),
                 gpio_get_level(PIN_ENC_A),    gpio_get_level(PIN_ENC_B),
                 (long)dw, (long)w, (unsigned long)s_wheel_err);

        /* Octets 2-5 du burst, decodes sous les deux hypotheses. Bouger sur un
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
        if (tour % 25 == 0) {
            pu = !pu;
            gpio_set_pull_mode(PIN_ENC_A, pu ? GPIO_PULLUP_ONLY : GPIO_FLOATING);
            gpio_set_pull_mode(PIN_ENC_B, pu ? GPIO_PULLUP_ONLY : GPIO_FLOATING);
            vTaskDelay(pdMS_TO_TICKS(5));
            ESP_LOGW(TAG, "molette : tirage interne %s -> AB=%d%d",
                     pu ? "ACTIF " : "coupe ",
                     gpio_get_level(PIN_ENC_A), gpio_get_level(PIN_ENC_B));
        }

        if (++tour % 25 == 0)
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
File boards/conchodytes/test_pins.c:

/* Pinout contract — Conchodytes mouse (U6).
 *
 * Read from the netlist at ~/Documents/GitHub/Conchodytes/hardware/pcb/ via
 * `kicad-cli export netlist` on 2026-08-25, NOT copied from the README: the
 * latter swapped left and right on the NC contacts (fixed since, but the
 * netlist remains the source of truth).
 *
 * This file exists for a specific reason: on this board, a pinout swap shows
 * up neither at compile time, nor at boot, nor even under naive use. The six
 * click contacts go in NO+NC pairs of the SAME button, and it is this
 * pairing that removes the bounce; crossing two pairs gives a firmware that
 * appears to work and produces phantom clicks. If the contract changes,
 * THIS file is updated first, then board.h.
 *
 * The values below were verified on real hardware on 2026-08-25:
 * pressing only the left click -> 26 edges on L, 0 on R.
 */
#include "test_framework.h"

/* ESP-IDF defines GPIO_NUM_* as an enum; on host we stub them. */
#ifndef GPIO_NUM_0
#define GPIO_NUM_0  0
#define GPIO_NUM_1  1
#define GPIO_NUM_2  2
#define GPIO_NUM_4  4
#define GPIO_NUM_5  5
#define GPIO_NUM_6  6
#define GPIO_NUM_7  7
#define GPIO_NUM_8  8
#define GPIO_NUM_9  9
#define GPIO_NUM_10 10
#define GPIO_NUM_11 11
#define GPIO_NUM_12 12
#define GPIO_NUM_13 13
#define GPIO_NUM_14 14
#define GPIO_NUM_15 15
#define GPIO_NUM_16 16
#define GPIO_NUM_17 17
#define GPIO_NUM_18 18
#define GPIO_NUM_21 21
#define GPIO_NUM_38 38
#define GPIO_NUM_39 39
#define GPIO_NUM_40 40
#define GPIO_NUM_41 41
#define GPIO_NUM_42 42
#define GPIO_NUM_47 47
#define GPIO_NUM_48 48
#define GPIO_NUM_NC (-1)
#define SPI2_HOST   1
#endif

#include "board.h"
#include "rf_slot.h"

/* Compile-time guards: the mouse has no matrix, no display, no trackpad.
 * A stray macro here would describe a peripheral that does not exist on
 * this board — we fail the build rather than let it slide. */
#ifdef BOARD_HAS_TRACKPAD_LOCAL
#error "the mouse has no trackpad: BOARD_HAS_TRACKPAD_LOCAL has no business in boards/conchodytes/board.h"
#endif
/* MATRIX_ROWS/COLS come from test_framework.h and are therefore always
 * defined here: we guard on ROWS0/COLS0, which only exist in a keyboard's
 * board.h. */
#ifdef ROWS0
#error "the mouse has no matrix switch: ROWS0 has no business in boards/conchodytes/board.h"
#endif
#ifdef COLS0
#error "the mouse has no matrix switch: COLS0 has no business in boards/conchodytes/board.h"
#endif
#ifdef BOARD_DISPLAY_BACKEND_ROUND
#error "the mouse has no display: BOARD_DISPLAY_BACKEND_ROUND has no business in boards/conchodytes/board.h"
#endif

/* GPIOs not wired on this board: strapping and octal PSRAM. */
static int conch_is_forbidden(int gpio)
{
    return gpio == 3 || gpio == 45 || gpio == 46 ||
           gpio == 35 || gpio == 36 || gpio == 37;
}

/* GPIOs committed elsewhere: native USB (19/20, module pins 13/14) and the
 * J1 programming connector (0, 43, 44). */
static int conch_is_reserved(int gpio)
{
    return gpio == 19 || gpio == 20 ||
           gpio == 0 || gpio == 43 || gpio == 44;
}

static void test_conch_sensor_pins(void)
{
    /* PMW3389: SPI shared with the nRF24, plus two dedicated lines. */
    TEST_ASSERT_EQ(BOARD_SNS_NCS_GPIO,    17, "sensor NCS = GPIO17 (pin 10)");
    TEST_ASSERT_EQ(BOARD_SNS_MOTION_GPIO, 18, "sensor MOTION = GPIO18 (pin 11)");

    /* fSCLK max = 2.0 MHz, Table 4 p. 15 of the PMW3389DM-T3QU datasheet.
     * Validated on hardware at this frequency on 2026-08-25. */
    TEST_ASSERT(BOARD_SNS_CLOCK_HZ <= 2000000, "PMW3389 fSCLK caps at 2 MHz");
    TEST_ASSERT_EQ(BOARD_SNS_SPI_MODE, 3, "PMW3389 in mode 3 (CPOL=1, CPHA=1)");
}

static void test_conch_radio_pins(void)
{
    /* The nRF24 shares SCK/MOSI/MISO with the sensor, but not the SPI mode:
     * mode 0 here, mode 3 for the PMW3389. */
    TEST_ASSERT_EQ(BOARD_NRF_SCK,  38, "SPI SCK shared sensor + radio");
    TEST_ASSERT_EQ(BOARD_NRF_MISO, 39, "SPI MISO shared");
    TEST_ASSERT_EQ(BOARD_NRF_MOSI, 40, "SPI MOSI shared");
    TEST_ASSERT_EQ(BOARD_NRF_CSN,  2,  "nRF24 CSN = GPIO2 (pin 38)");
    TEST_ASSERT_EQ(BOARD_NRF_CE,   1,  "nRF24 CE = GPIO1 (pin 39)");
    TEST_ASSERT_EQ(BOARD_NRF_IRQ,  41, "nRF24 IRQ = GPIO41 (pin 34)");

    /* Dongle slot 2. boards/kase_dongle/board.h annotates BOARD_NRF2_* as
     * "mouse slot (Conchodytes), channel 0x52" — both sides must
     * agree or the link never establishes. */
    TEST_ASSERT_EQ(BOARD_NRF_ADDR_SUFFIX, 0x02, "address suffix = mouse slot");
    TEST_ASSERT_EQ(BOARD_NRF_CHANNEL, RF_CH_MOUSE_DONGLE, "channel == channel plan");
    TEST_ASSERT_EQ(BOARD_NRF_CHANNEL,     0x52, "slot 2 channel, cf. dongle board.h");
}

static void test_conch_click_pairs(void)
{
    /* THE test of this file. Each button has its NO and its NC, and the
     * debounce reads BOTH. Crossing the pairs gives a firmware that produces
     * phantom clicks without any tool noticing.
     *
     * ⚠ The README stated LEFT_NC = GPIO4 and RIGHT_NC = GPIO5. The netlist
     * says the opposite: GPIO4 -> SW2.3 (RIGHT click, R109), GPIO5 -> SW1.3
     * (LEFT click, R108). Verified on the board: pressing only the left click
     * produced 26 edges on L and 0 on R.
     */
    TEST_ASSERT_EQ(BOARD_SW_LEFT_GPIO,     10, "left click NO = GPIO10");
    TEST_ASSERT_EQ(BOARD_SW_LEFT_NC_GPIO,   5, "left click NC = GPIO5, NOT GPIO4");
    TEST_ASSERT_EQ(BOARD_SW_RIGHT_GPIO,    11, "right click NO = GPIO11");
    TEST_ASSERT_EQ(BOARD_SW_RIGHT_NC_GPIO,  4, "right click NC = GPIO4, NOT GPIO5");
    TEST_ASSERT_EQ(BOARD_SW_MID_GPIO,      12, "middle click NO = GPIO12");
    TEST_ASSERT_EQ(BOARD_SW_MID_NC_GPIO,    6, "middle click NC = GPIO6");

    /* The three NCs are on 4/5/6 and the three NOs on 10/11/12: no NC should
     * end up in the NO range, and vice versa. A typo swapping an NO and an NC
     * would produce a button whose two lines are on the same side — invisible
     * to the equalities above if they were all updated together. */
    const int nc[] = { BOARD_SW_LEFT_NC_GPIO, BOARD_SW_RIGHT_NC_GPIO, BOARD_SW_MID_NC_GPIO };
    const int no[] = { BOARD_SW_LEFT_GPIO,    BOARD_SW_RIGHT_GPIO,    BOARD_SW_MID_GPIO };
    for (unsigned i = 0; i < 3; i++) {
        TEST_ASSERT(nc[i] >= 4  && nc[i] <= 6,  "the three NCs are on GPIO4-6");
        TEST_ASSERT(no[i] >= 10 && no[i] <= 12, "the three NOs are on GPIO10-12");
    }
}

static void test_conch_wheel_pins(void)
{
    TEST_ASSERT_EQ(BOARD_ENC_A_GPIO, 7, "encoder channel A = GPIO7 (pin 7)");
    TEST_ASSERT_EQ(BOARD_ENC_B_GPIO, 9, "encoder channel B = GPIO9 (pin 17)");
}

static void test_conch_battery_pin(void)
{
    /* WARNING: GPIO13 = ADC2_CH2, and on ESP32-S3 ADC2 is shared with the
     * WiFi driver: as long as the battery reading is there, WiFi is forbidden
     * on this board. No consequence today (the radio is an nRF24 and the
     * firmware never turns WiFi on) but it is a mortgage.
     * NOTES-V2.md point 7 plans to move the reading to GPIO8 / ADC1_CH7
     * in v2. When that is done, this value changes first. */
    TEST_ASSERT_EQ(BOARD_VBAT_SENSE_GPIO, 13, "gauge on ADC2_CH2 in v1");
}

/* All the board's pins, in a single place — the next three tests
 * depend on it and must see exactly the same list. */
#define CONCH_ALL_PINS \
    BOARD_SNS_NCS_GPIO, BOARD_SNS_MOTION_GPIO, \
    BOARD_NRF_SCK, BOARD_NRF_MISO, BOARD_NRF_MOSI, \
    BOARD_NRF_CSN, BOARD_NRF_CE, BOARD_NRF_IRQ, \
    BOARD_SW_LEFT_GPIO,  BOARD_SW_LEFT_NC_GPIO, \
    BOARD_SW_RIGHT_GPIO, BOARD_SW_RIGHT_NC_GPIO, \
    BOARD_SW_MID_GPIO,   BOARD_SW_MID_NC_GPIO, \
    BOARD_ENC_A_GPIO, BOARD_ENC_B_GPIO, \
    BOARD_VBAT_SENSE_GPIO

static void test_conch_no_forbidden_gpio(void)
{
    const int pins[] = { CONCH_ALL_PINS };
    for (unsigned i = 0; i < sizeof(pins) / sizeof(pins[0]); i++)
        TEST_ASSERT(!conch_is_forbidden(pins[i]), "no pin on an unwired GPIO");
}

static void test_conch_no_reserved_gpio(void)
{
    const int pins[] = { CONCH_ALL_PINS };
    for (unsigned i = 0; i < sizeof(pins) / sizeof(pins[0]); i++)
        TEST_ASSERT(!conch_is_reserved(pins[i]), "no pin on native USB or J1");
}

static void test_conch_no_pin_used_twice(void)
{
    const int pins[] = { CONCH_ALL_PINS };
    const unsigned n = sizeof(pins) / sizeof(pins[0]);
    for (unsigned i = 0; i < n; i++)
        for (unsigned j = i + 1; j < n; j++)
            TEST_ASSERT(pins[i] != pins[j], "no GPIO duplicated across the whole board");
}

void test_conchodytes_pins(void)
{
    printf("\n-- Conchodytes pinout (netlist contract 2026-08-25) --\n");
    test_conch_sensor_pins();
    test_conch_radio_pins();
    test_conch_click_pairs();
    test_conch_wheel_pins();
    test_conch_battery_pin();
    test_conch_no_forbidden_gpio();
    test_conch_no_reserved_gpio();
    test_conch_no_pin_used_twice();
}
